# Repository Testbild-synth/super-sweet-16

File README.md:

# "Super Sweet 16" - 16 Step Knob-per-function Sequencer Module for Eurorack
For a while now I've been looking for a through hole diy eurorack sequencer that is as hands-on as the Baby8 but with comfort features 
you would maybe not have with an analog/cmos design. The outcome of my struggle is this module. It is a 16-step sequencer with the following functions:
- variable sequence length up to 16 steps
- Cascading (meaning you can connect multiple to get 32/48/etc steps)
- Builtin quantizer with multiple scales (off, chromatic, major, minor, blues, pentatonic)
- 1-5 octave selectable range
- Holding or pausing notes for each steps
- 2 x Gate and 2x CV out
- splittable (meaning you can have 2 channels for sequence lengths lower than 8)
- Slide pot with CV input for held steps
- Internal clock
- Runs Forwards, backwards and randomly selected steps

## Status - Second revision comfirmed working! code needs a bit of cleanup and I need to upload a youtube explaining the use. Also has a version with the SMD package of the MCP4728 now but that one is not tested!

## Hardware and build

I really wanted this to go on one pcb and while its a bit cramped, it works and I think the build is still doable. 
the panel is 19hp, which is kind of a weird size. If people message me about it I might change it to 20 so that there's a bit more space between knobs but for now I'm fine like this.

you need three ICs: 
- An arduino nano v3, 
- a 4067 mux breakout board (like [this](https://www.ebay.de/itm/273816945682), there's a bunch of these any that has this form factor will do.
- A 4728 dac breakout board (slim form factor, like like [this](https://www.play-zone.ch/de/gy-mcp4728-breakout-quad-i2c-dac-mit-eeprom.html). I wanted through hole only and I had a bunch lying around. If these are hard to source for you, look at the smd_dac versions of the circuitboard (should work but have not been verified yet!).

For the build, I would suggest you go in the following order:
1. diodes
2. headers for arduino and breakout boards
3. resistors (this is important because there are resistors across the input jacks that you should definitely do before the jacks)
4. jacks, pots and the rest
Since the board is a bit cramped you might have to think about the order a bit while building, I didn't have major problems but your mileage might vary.

you can order the pcbs as is with the gerbers provided from any pcb service, I use jlc. Make sure to use leadfree surface finish for the panel as you will be touching silver areas.
**I still have a bunch of PCBs and panels leftover, if you're in the EU and don't wanna order yourself I can sell you a set :)**

## Software

code subfolder contains finished arduino sketch. 

for your arduino to compile and upload properly you need the adafruit_4728 library and the Analog-digital-multiplexers library (https://docs.arduino.cc/libraries/analog-digital-multiplexers/).

To make 16 channels and per-step switches work with an arduino nano and one mux on one pcb, I had to cut a few corners.
The result is that if you have cold solder joints or some contacts are not soldered perfectly you might have a bit of MUX crosstalk (meaning that the frequency at which the mux is switched is so high that there is leftover charge from the last reading).
To check, do the following:
- Set the sequencer to a step length smaller than 8 (see operation)
- plug both CV outputs into something you can read or an oscillator so you will notice changes
- Make sure scale pot is turned all the way counterclockwise (no quantization)
- Turn both CV pots of the active step individually and make sure one does not affect the other (only the output of the pot you turn should change). Turn the SLIDE pot and make sure it doesn't affect the output values.

Mine is fine as is but you can increase the CROSSTALK_DELAY_MS variable in the code. this might decrease crosstalk but increase latency. If you still get problems, redo all solder joints. 
If you still get problems after that tell me and we can talk about changing some resistors, but as I said mine works as is so this might not be needed.

## Operation

Basic operation: 
- Plug in clock into clock input. Pots change value from 0-5V, 
switch changes gate behavior:
  - middle position: "on", gate gets triggered on step change and holds until clock input goes low
  - top position: "hold", gate gets triggered and stays on. You can apply slide to the step value
  - bottom position: "off", no gate gets output
- "Scale" pot applies quantization from left to right: none, chromatic, major, minor, melodic minor, blues, pentatonic, fith and octave, octave.
- "Order" Pot changes sequence order. from left to right: forwards, backwards, random (calculated again each time you switch back and forth)
- "Slide" Pot applies slide (slows down cv change) for all steps where "Hold" is on
- "STEP" button goes to next step
- "RESET STEP" button/CV resets the sequence

Menu:
**Press and hold "reset step"** to get into menu mode. Now you can change the following parameters:
- pressing "STEP" button for a short amount of time turns internal clock on and off. CV leds will blink twice quickly to indicate that the clock is switched on/off.
- holdling "STEP" button for more than a second allows you to change internal clock frequency with the "ORDER" pot. and LED will blink indicating the clock speed.
- turning "SLIDE" pot will change sequence length from 2 to 16. Sequences under 8 automatically enable different values for both channels. LEDs indicate new step length
- turning "SCALE" pot will change maximum output voltage between 1 and 5 volts. this will limit the octaves you want to use but allows more detailed tuning in for step values

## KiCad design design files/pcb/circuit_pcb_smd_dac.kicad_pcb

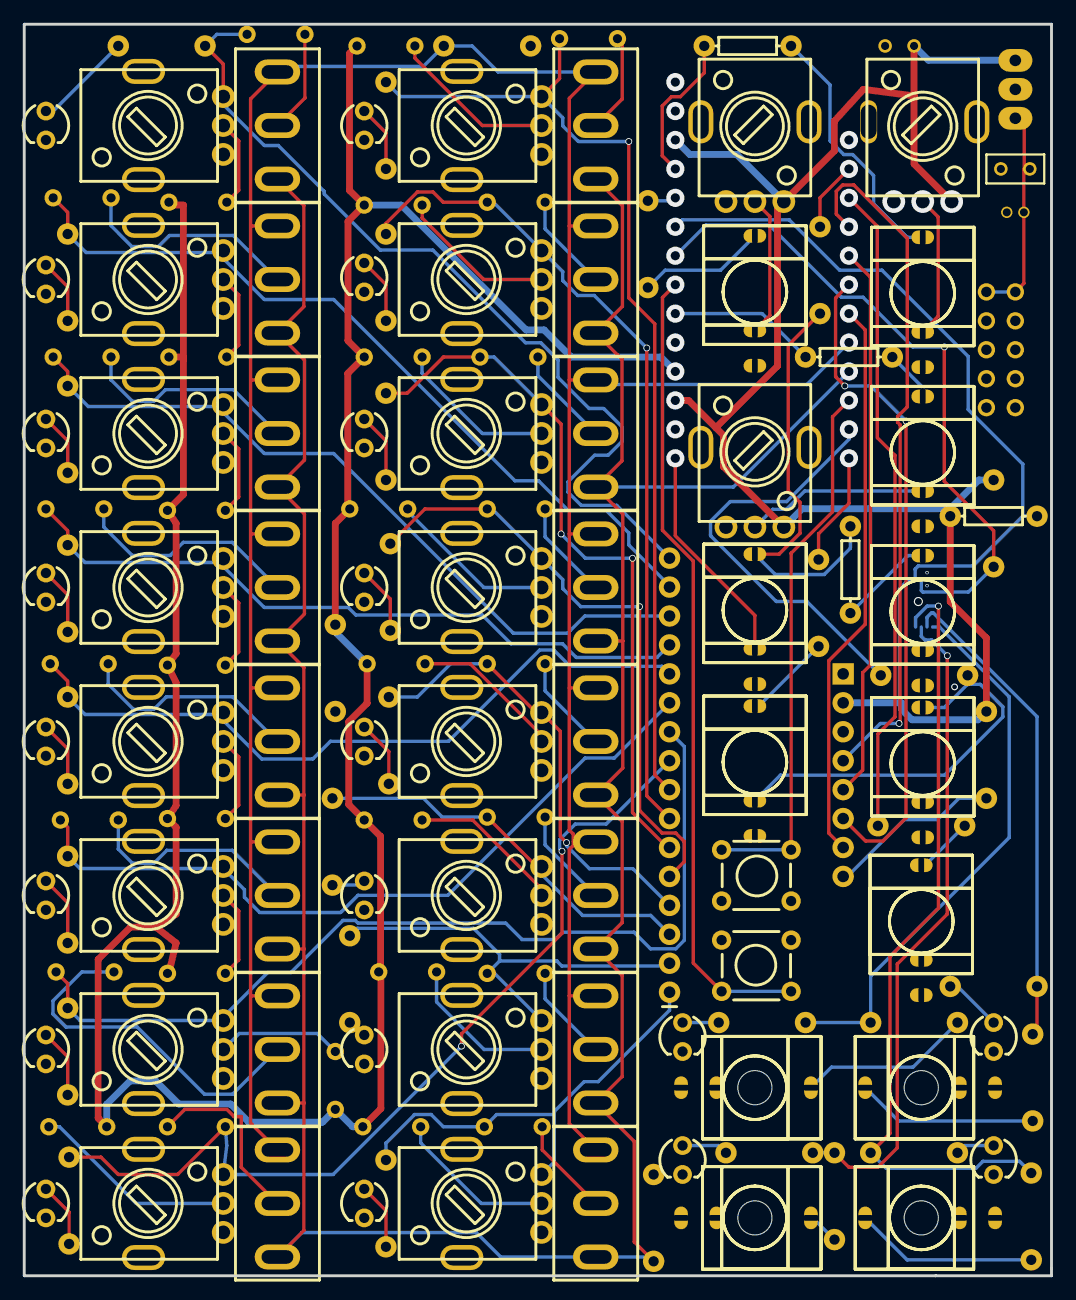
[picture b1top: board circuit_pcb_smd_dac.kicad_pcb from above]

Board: 2 copper layers, 90.2 x 109.9 mm, 137 parts (0 on the bottom side), 88 nets.

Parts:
C1: 10u; CAP-D4.0×F1.5
C2, C3: 100n; RAD-0.1
D1, D2, D3, D4, D5, D6, D7, D8, D9, D10, D11, D12, D13, D14, D15, D16, D17, D18, D19, D20, D21, D22, D23, D24, D25, D26, D27, D28, D29, D30, D31, D32: BAT43; DIODE
J9: G1; THONKICONN_1
J10: CV1; THONKICONN_1
J12: CV2; THONKICONN_1
J13: G2; THONKICONN_1
LED1, LED2, LED3, LED4, LED5, LED6, LED7, LED8, LED9, LED10, LED11, LED12, LED13, LED14, LED15, LED16, LED17, LED18, LED19, LED20: LED TBR; LED-3MM/2.54
P1, P2, P3, P4, P5, P6, P7, P8, P9, P10, P11, P12, P13, P14, P15, P16: 10-100k; R09-5KΩ
P17: 16x1_Mux_board_CD74HC4067; CD74HC4067
P18: POWER; EURORACK SHROUDED POWER 10 PIN
R1, R2, R3, R4, R5, R6, R7, R8, R9, R10, R11, R12, R13, R14, R15, R16: 10k; R_AXIAL-0.3
R17, R18, R19, R26, R27, R28, R29: 22k; R_AXIAL-0.3
R20, R21: 3k3; R_AXIAL-0.3
R22, R23, R31, R32: 4.7k; R_AXIAL-0.3
R24, R25, R30, R33, R34: 1k; R_AXIAL-0.3
R35: 100K; R_AXIAL-0.3
R36: 100k; R_AXIAL-0.3
R38: 1M; R_AXIAL-0.3
R40: 100; R_AXIAL-0.3
S1, S2, S3, S4, S5, S6, S7, S8, S9, S10, S11, S12, S13, S14, S15, S16: SPDT; TOGGLE SWITCH SPDT RED 3 PIN ON-OFF-ON 3 SPDT SMALL AC 6A/1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
SCALE: 10-100k; R09-5KΩ
SLIDE_AMT: 10-100k; R09-5KΩ
U2: STEP; PUSHBUTTON
U3: SET_STEP; PUSHBUTTON
U4: 7805
U5: MCP4728; MSOP-10_L3.0-W3.0-P0.50-LS5.0-BL

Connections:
ARD_5: C3.2, P17.18, R20.1, R21.1, R40.1, SCALE.3, SLIDE_AMT.3, U4.3, U5.1
A_IN: D1.2, D2.2, D3.2, D4.2, D5.2, D6.2, D7.2, D8.2, D9.2, D10.2, D11.2, D12.2, D13.2, D14.2, D15.2, D16.2, R38.1
C2_2: C1.1, C2.2, P18.1, U4.1
D2_1: D2.1, P2.2
D3_1: D3.1, P3.2
D4_1: D4.1, P4.2
D5_1: D5.1, P5.2
D6_1: D6.1, P6.2
D7_1: D7.1, P7.2
D8_1: D8.1, P8.2
D9_1: D9.1, P9.2
D10_1: D10.1, P10.2
D11_1: D11.1, P11.2
D12_1: D12.1, P12.2
D13_1: D13.1, P13.2
D14_1: D14.1, P14.2
D15_1: D15.1, P15.2
GND: C1.2, C2.1, C3.1, J9.1, J10.1, J12.1, J13.1, LED1.2, LED2.2, LED3.2, LED4.2, LED5.2, LED6.2, LED7.2, LED8.2, LED9.2, LED10.2, LED11.2, LED12.2, LED13.2, LED14.2, LED15.2, LED16.2, LED17.2, LED18.2, LED19.2, LED20.2, P1.1, P2.1, P3.1, P4.1, P5.1, P6.1, P7.1, P8.1, P9.1, P10.1, P11.1, P12.1, P13.1, P14.1, P15.1, P16.1, P17.17, P18.2, P18.3, P18.4, R35.1, R36.2, R38.2, SCALE.1, SLIDE_AMT.1, U2.3, U2.4, U3.3, U3.4, U4.2, U5.4, U5.10
J8_3: R29.2, R30.2
J10_3: J10.3, R25.2
J12_3: J12.3, R33.2
J13_3: J13.3, R34.2
LED2_1: LED2.1, R2.2
LED3_1: LED3.1, R3.2
LED4_1: LED4.1, R4.2
LED5_1: LED5.1, R5.2
LED6_1: LED6.1, R6.2
LED7_1: LED7.1, R7.2
LED8_1: LED8.1, R8.2
LED9_1: LED9.1, R9.2
LED10_1: LED10.1, R10.2
LED11_1: LED11.1, R11.2
LED12_1: LED12.1, R12.2
LED13_1: LED13.1, R13.2
LED14_1: LED14.1, R14.2
LED15_1: LED15.1, R15.2
MUX_1: D18.1, P1.3, P17.1, R1.1
MUX_2: D17.1, P2.3, P17.2, R2.1
MUX_3: D19.1, P3.3, P17.3, R3.1
MUX_4: D20.1, P4.3, P17.4, R4.1
MUX_5: D21.1, P5.3, P17.5, R5.1
MUX_6: D22.1, P6.3, P17.6, R6.1
MUX_7: D23.1, P7.3, P17.7, R7.1
MUX_8: D24.1, P8.3, P17.8, R8.1
MUX_9: D25.1, P9.3, P17.9, R9.1
MUX_10: D26.1, P10.3, P17.10, R10.1
MUX_11: D27.1, P11.3, P17.11, R11.1
MUX_12: D28.1, P12.3, P17.12, R12.1
MUX_13: D29.1, P13.3, P17.13, R13.1
MUX_14: D30.1, P14.3, P17.14, R14.1
MUX_15: D31.1, P15.3, P17.15, R15.1
MUX_16: D32.1, P16.3, P17.16, R16.1
O_1: R22.1, R24.1, U5.6
O_2: R31.1, R34.1, U5.7
O_3: R23.1, R25.1, U5.8
O_4: R32.1, R33.1, U5.9
P1_2: D1.1, P1.2
P16_2: D16.1, P16.2
P17_24: P17.24, R40.2
PAUSE: R35.2, S1.3, S2.3, S3.3, S4.3, S5.3, S6.3, S7.3, S8.3, S9.3, S10.3, S11.3, S12.3, S13.3, S14.3, S15.3, S16.3
R1_2: LED1.1, R1.2
R16_2: LED16.1, R16.2
R22_2: LED17.1, R22.2
R23_2: LED18.1, R23.2
R24_2: J9.3, R24.2
R31_2: LED19.1, R31.2
R32_2: LED20.1, R32.2
S1_2: D18.2, S1.2
S2_2: D17.2, S2.2
S3_2: D19.2, S3.2
S4_2: D20.2, S4.2
S5_2: D21.2, S5.2
S6_2: D22.2, S6.2
S7_2: D23.2, S7.2
S8_2: D24.2, S8.2
S9_2: D25.2, S9.2
S10_2: D26.2, S10.2
S11_2: D27.2, S11.2
S12_2: D28.2, S12.2
S13_2: D29.2, S13.2
S14_2: D30.2, S14.2
S15_2: D31.2, S15.2
S16_2: D32.2, S16.2
SCL: R21.2, U5.2
SDA: R20.2, U5.3
SET_STEP: U3.1, U3.2
SLIDE: R36.1, S1.1, S2.1, S3.1, S4.1, S5.1, S6.1, S7.1, S8.1, S9.1, S10.1, S11.1, S12.1, S13.1, S14.1, S15.1, S16.1
STEP_IN: U2.1, U2.2

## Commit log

2023-05-14 file upload p1
2023-05-14 code and schematic upload
2023-05-15 Update README.md
    added a bunch of stuff to readme
2023-05-15 upload gerber images
2023-06-14 Added first wip version for smd dac - not tested!
2025-02-04 clean up bom
2025-02-04 took need to update bom out or readme
